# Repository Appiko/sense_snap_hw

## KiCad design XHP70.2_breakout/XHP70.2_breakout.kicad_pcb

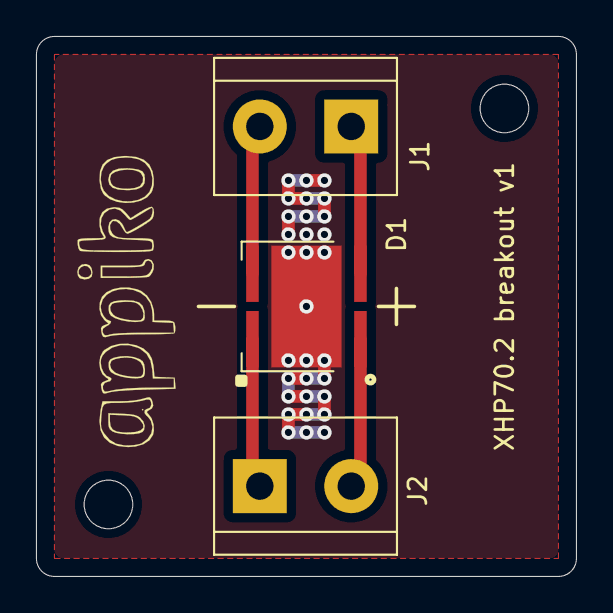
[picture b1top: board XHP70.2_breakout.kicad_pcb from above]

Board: 2 copper layers, 30.0 x 30.0 mm, 3 parts (0 on the bottom side), 4 nets.

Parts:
D1: XHP70.2; LED_Cree-XHP70
J1, J2: Screw_Terminal_01x02; TerminalBlock_bornier-2_P5.08mm

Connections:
unnamed: D1.1, J1.2
unnamed: D1.2, J2.1
unnamed: D1.3, J2.2
unnamed: D1.4, J1.1

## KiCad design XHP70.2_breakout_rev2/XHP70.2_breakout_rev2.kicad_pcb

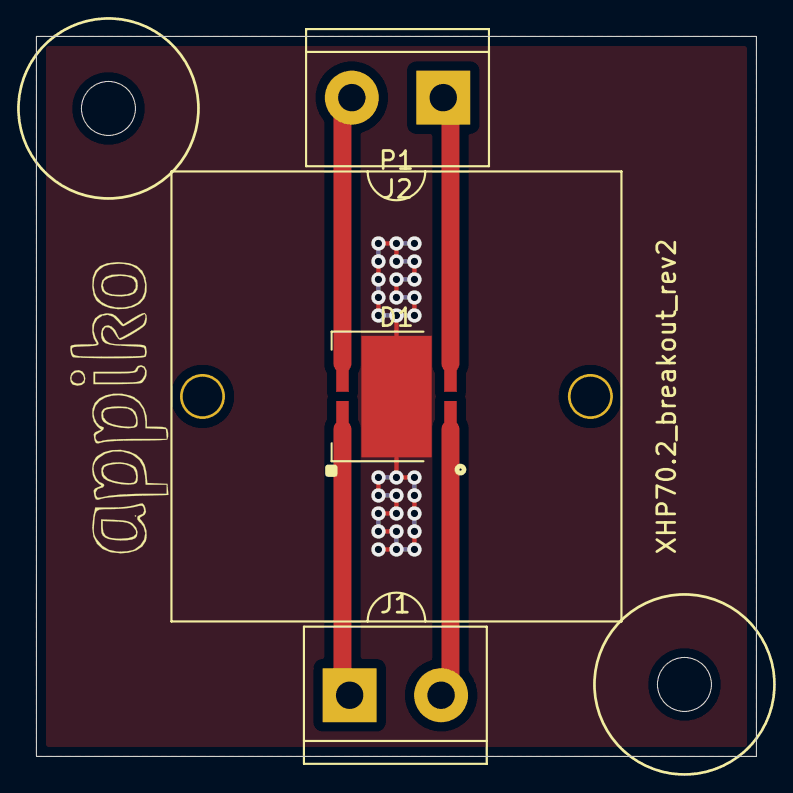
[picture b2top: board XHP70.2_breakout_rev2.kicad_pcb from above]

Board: 2 copper layers, 40.0 x 40.0 mm, 6 parts (0 on the bottom side), 4 nets.

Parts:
D1: XHP70.2; LED_Cree-XHP70
J1, J2: Screw_Terminal_01x02; TerminalBlock_bornier-2_P5.08mm
MK1, MK2: Mounting_Hole_3mm; MountingHole_3mm
P1: CA16372_HB-SQ-WWW

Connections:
unnamed: D1.1, J2.2
unnamed: D1.2, J1.1
unnamed: D1.3, J1.2
unnamed: D1.4, J2.1

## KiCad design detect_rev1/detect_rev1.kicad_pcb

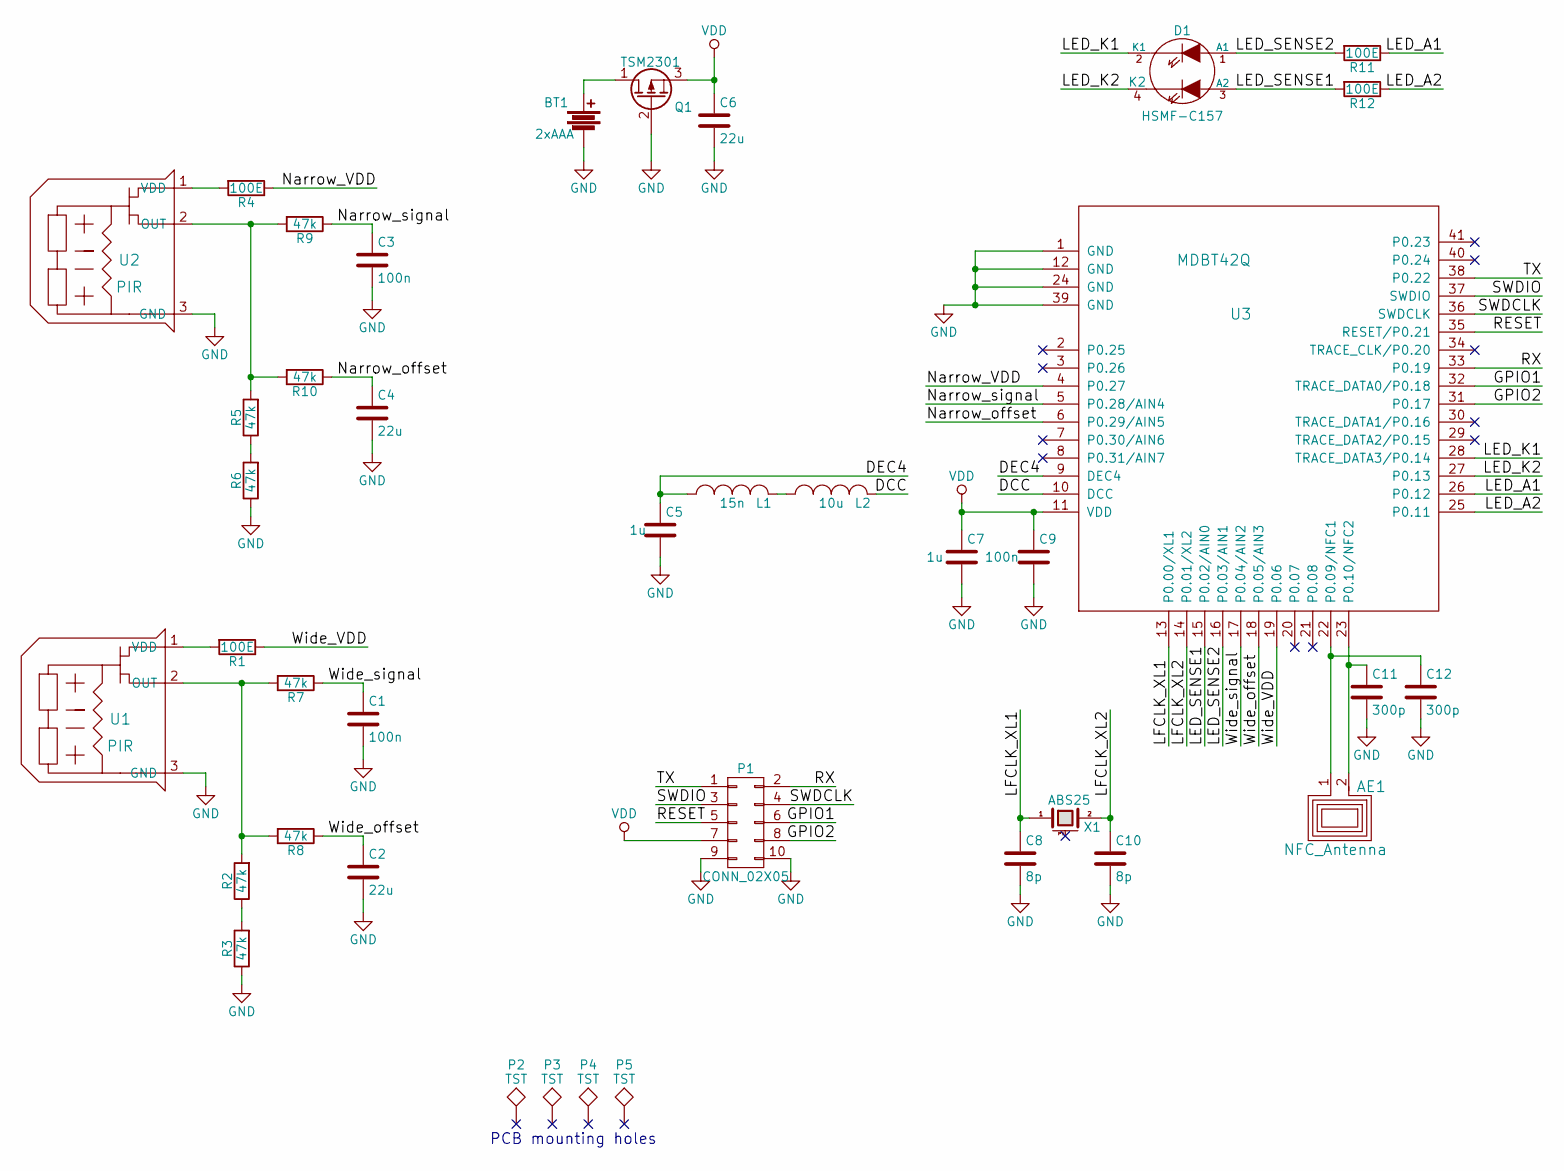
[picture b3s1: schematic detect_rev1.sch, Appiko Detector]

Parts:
AE1: NFC_Antenna; GS2
BT1: 2xAAA; AAA_holder_2468; Part Number 2468
C1, C3, C9: 100n; C_0805
C2, C4, C6: 22u; C_1206; Rating >10V
C5, C7: 1u; C_0805
C8, C10: 8p; C_0805
C11, C12: 300p; C_0805
D1: HSMF-C157; HSMF-C15x; Part Number HSMF-C157
L1: 15n; C_0603
L2: 10u; C_0805
P1: CONN_02X05; Berg_5x2Conn
P2, P3, P4, P5: TST; MountingHole_4.3mm_M4
Q1: TSM2301; Part Number TSM2301CX
R1, R4, R11, R12: 100E; R_0805
R2, R3, R5, R6, R7, R8, R9, R10: 47k; R_0805
U1: PIR; PIR_TO5
U2: PIR; PIR_TO5; Part Number D203B LHi968
U3: MDBT42Q; mdbt42Q
X1: ABS25; ABS25-32.768; Part Number ABS25-32.768KHZ-6-T

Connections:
/DCC: L2.2, U3.10 (DCC)
/DEC4: C5.1, L1.1, U3.9 (DEC4)
/GPIO1: P1.6, U3.32 (TRACE_DATA0/P0.18)
/GPIO2: P1.8, U3.31 (P0.17)
/LED_A1: R11.1, U3.26 (P0.12)
/LED_A2: R12.1, U3.25 (P0.11)
/LED_K1: D1.2 (K1), U3.28 (TRACE_DATA3/P0.14)
/LED_K2: D1.4 (K2), U3.27 (P0.13)
/LED_SENSE1: D1.3 (A2), R12.2, U3.15 (P0.02/AIN0)
/LED_SENSE2: D1.1 (A1), R11.2, U3.16 (P0.03/AIN1)
/LFCLK_XL1: C8.1, U3.13 (P0.00/XL1), X1.1
/LFCLK_XL2: C10.1, U3.14 (P0.01/XL2), X1.2
/Narrow_VDD: R4.1, U3.4 (P0.27)
/Narrow_offset: C4.1, R10.1, U3.6 (P0.29/AIN5)
/Narrow_signal: C3.1, R9.1, U3.5 (P0.28/AIN4)
/RESET: P1.5, U3.35 (RESET/P0.21)
/RX: P1.2, U3.33 (P0.19)
/SWDCLK: P1.4, U3.36 (SWDCLK)
/SWDIO: P1.3, U3.37 (SWDIO)
/TX: P1.1, U3.38 (P0.22)
/Wide_VDD: R1.1, U3.19 (P0.06)
/Wide_offset: C2.1, R8.1, U3.18 (P0.05/AIN3)
/Wide_signal: C1.1, R7.1, U3.17 (P0.04/AIN2)
GND: BT1.2, C1.2, C2.2, C3.2, C4.2, C5.2, C6.2, C7.2, C8.2, C9.2, C10.2, C11.2, C12.2, P1.9, P1.10, Q1.2 (G), R3.1, R6.1, U1.3 (GND), U2.3 (GND), U3.1 (GND), U3.12 (GND), U3.24 (GND), U3.39 (GND)
unnamed: AE1.1, C12.1, U3.22 (P0.09/NFC1)
unnamed: AE1.2, C11.1, U3.23 (P0.10/NFC2)
unnamed: BT1.1, Q1.1 (D)
unnamed: L1.2, L2.1
unnamed: R1.2, U1.1 (VDD)
unnamed: R2.1, R3.2
unnamed: R2.2, R7.2, R8.2, U1.2 (OUT)
unnamed: R4.2, U2.1 (VDD)
unnamed: R5.1, R6.2
unnamed: R5.2, R9.2, R10.2, U2.2 (OUT)
VDD: C6.1, C7.1, C9.1, P1.7, Q1.3 (S), U3.11 (VDD)

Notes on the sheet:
PCB mounting holes

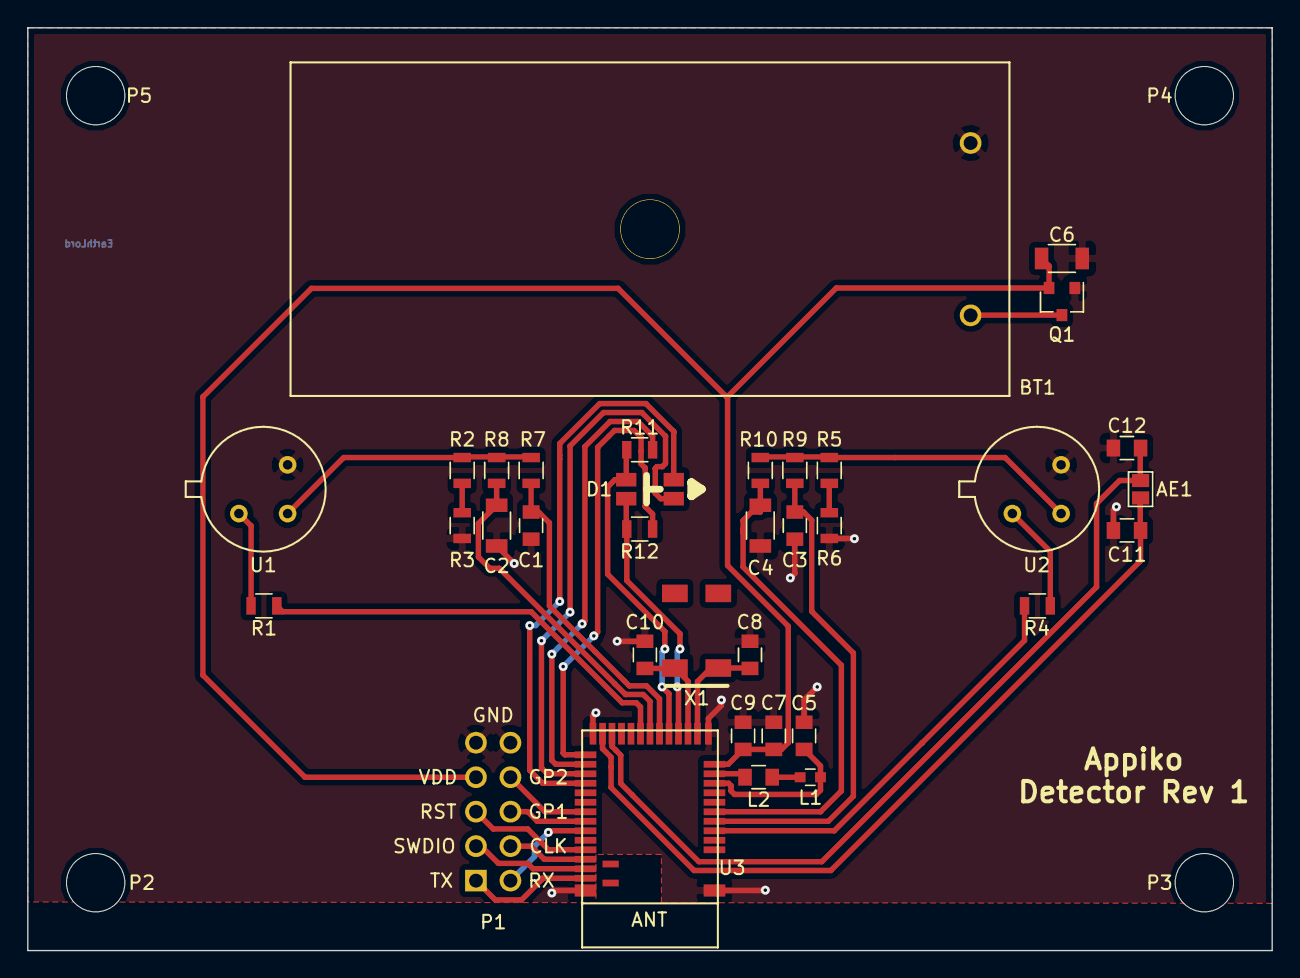
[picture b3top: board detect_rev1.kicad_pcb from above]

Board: 2 copper layers, 91.7 x 68.0 mm, 39 parts (0 on the bottom side), 35 nets.

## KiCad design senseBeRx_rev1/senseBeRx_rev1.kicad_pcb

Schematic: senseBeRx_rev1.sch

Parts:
BT1: Battery; BT_Symbol
C1, C3: 1uF; C_0603_1608Metric_Pad1.05x0.95mm_HandSolder
C2: 10uF; C_0805_2012Metric_Pad1.15x1.40mm_HandSolder
C4, C6: 8pF; C_0603_1608Metric_Pad1.05x0.95mm_HandSolder
C5, C7, C8: 100nF; C_0603_1608Metric_Pad1.05x0.95mm_HandSolder
D1: APBD3224SURKCGKC-F01; LED_APBD3224SURKCGKC-F01
D2: D_Photo; LED_D5.0mm
J1, J2: SJ2-35863B1-SMT
L1: 15nH; L_0603_1608Metric_Pad1.05x0.95mm_HandSolder
L2: 10nH; L_0603_1608Metric_Pad1.05x0.95mm_HandSolder
MK1, MK2: Mounting_Hole; MountingHole_3.2mm_M3
P1: CONN_02X05; prog_connect
Q1: TSM2301; SOT-23_Handsoldering
Q2, Q3, Q4: SI2302; SOT-23_Handsoldering
R1, R4, R5, R7, R8, R9: 100k; R_0603_1608Metric_Pad1.05x0.95mm_HandSolder
R2: 33; R_0603_1608Metric_Pad1.05x0.95mm_HandSolder
R3: 24; R_0603_1608Metric_Pad1.05x0.95mm_HandSolder
R6: 3M; R_0603_1608Metric_Pad1.05x0.95mm_HandSolder
SW1: SW_DPST; SW_TH_Tactile_Omron_B3F-10xx
U1: MDBT42Q; mdbt42Q
U2: TSSP4056; Vishay_MINIMOLD-3Pin
Y1: T38 Mercury; Crystal_C38-LF_D3.0mm_L8.0mm_Horizontal

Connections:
/BUTTON: C8.2, SW1.4, U1.21
/CAM_JACK: J1.4, R8.2, U1.25
/DCC: L2.2, U1.10
/DEC4: C1.2, L1.1, U1.9
/FOCUS: J1.3, U1.26
/GPIO1: P1.6, U1.33
/GPIO2: P1.7, U1.32
/LED_GREEN: Q2.1 (G), R1.1, U1.2
/LED_RED: Q3.1 (G), R4.1, U1.3
/LFCLK_XL1: C4.2, U1.13, Y1.1
/LFCLK_XL2: C6.2, U1.14, Y1.2
/LIGHT_SENSE: D2.1, R5.2, U1.18
/RESET: P1.5, U1.35
/RX: P1.8, U1.31
/RX_EN: Q4.1 (G), R7.1, U1.20
/RX_OUT: U1.19, U2.1
/RX_UARTRX: J2.3, U1.29
/RX_UARTTX: J2.2, U1.30
/SWDCLK: P1.3, U1.36
/SWDIO: P1.1, U1.37
/TRIGGER: J1.2, U1.27
/TX: P1.2, U1.34
/UART_JACK: J2.4, R9.2, U1.28
GND: BT1.2, C1.1, C2.2, C3.1, C4.1, C5.1, C6.1, C7.2, C8.1, D2.2, J1.1, J2.1, P1.9, P1.10, Q1.1 (G), Q2.2 (S), Q3.2 (S), Q4.2 (S), R1.2, R4.2, R6.2, R7.2, SW1.3, U1.1, U1.12, U1.24, U1.39
unnamed: BT1.1, Q1.3 (D)
unnamed: D1.2, R2.2
unnamed: D1.4, R3.2
unnamed: L1.2, L2.1
unnamed: Q2.3 (D), R3.1
unnamed: Q3.3 (D), R2.1
unnamed: Q4.3 (D), R6.1, U2.2
VDD: C2.1, C3.2, C5.2, C7.1, D1.1, D1.3, P1.4, Q1.2 (S), R5.1, R8.1, R9.1, U1.8, U1.11, U2.3

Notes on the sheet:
Two 1.2V AA Batteries
Reverse polarity protection
Two Color (Green/Red) LED
A momentary push button with debouncing cap to switch to config. mode
To use the Internal DC/DC Converter we need an LC Filter
For programming and debugging the nRF controller
Low freq. Crystal 32.768 kHz
IR pattern receiver with an enable switch
Ambient light sensing
Port to trigger the camera
Port for the UART communication between the SenseBe Rx and Tx units

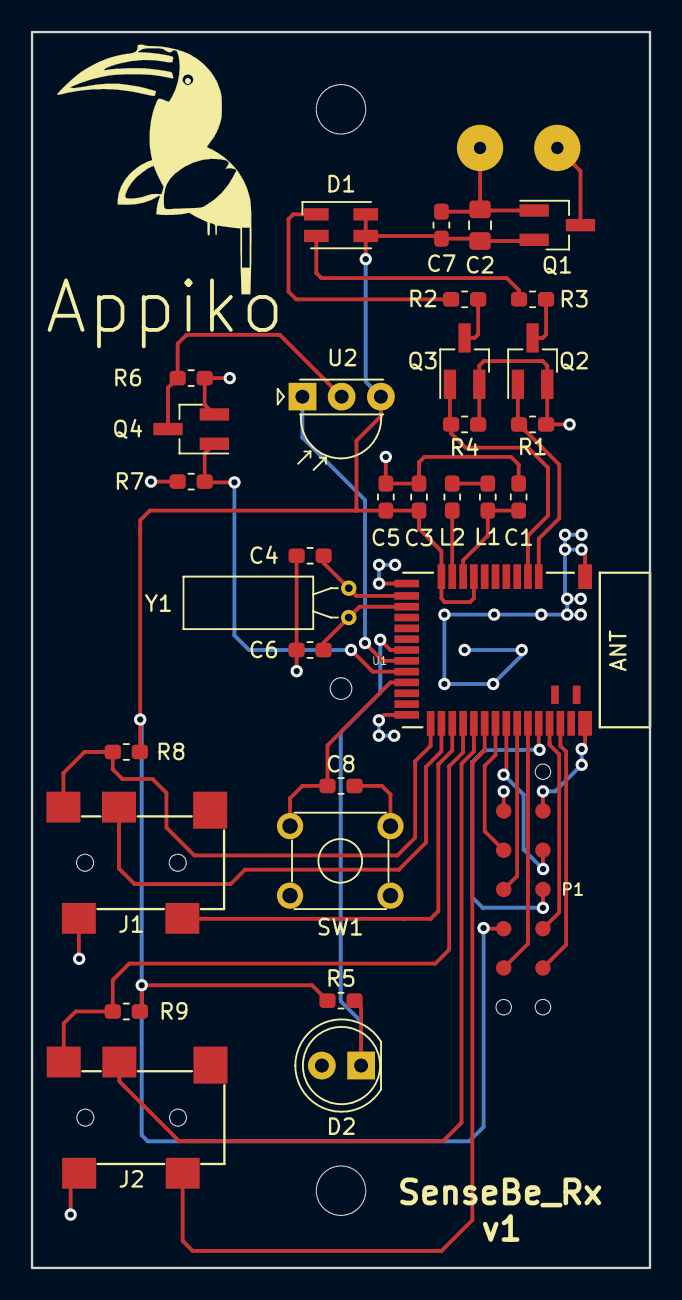
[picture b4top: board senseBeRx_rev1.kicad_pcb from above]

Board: 2 copper layers, 40.0 x 80.0 mm, 33 parts (1 on the bottom side), 32 nets.

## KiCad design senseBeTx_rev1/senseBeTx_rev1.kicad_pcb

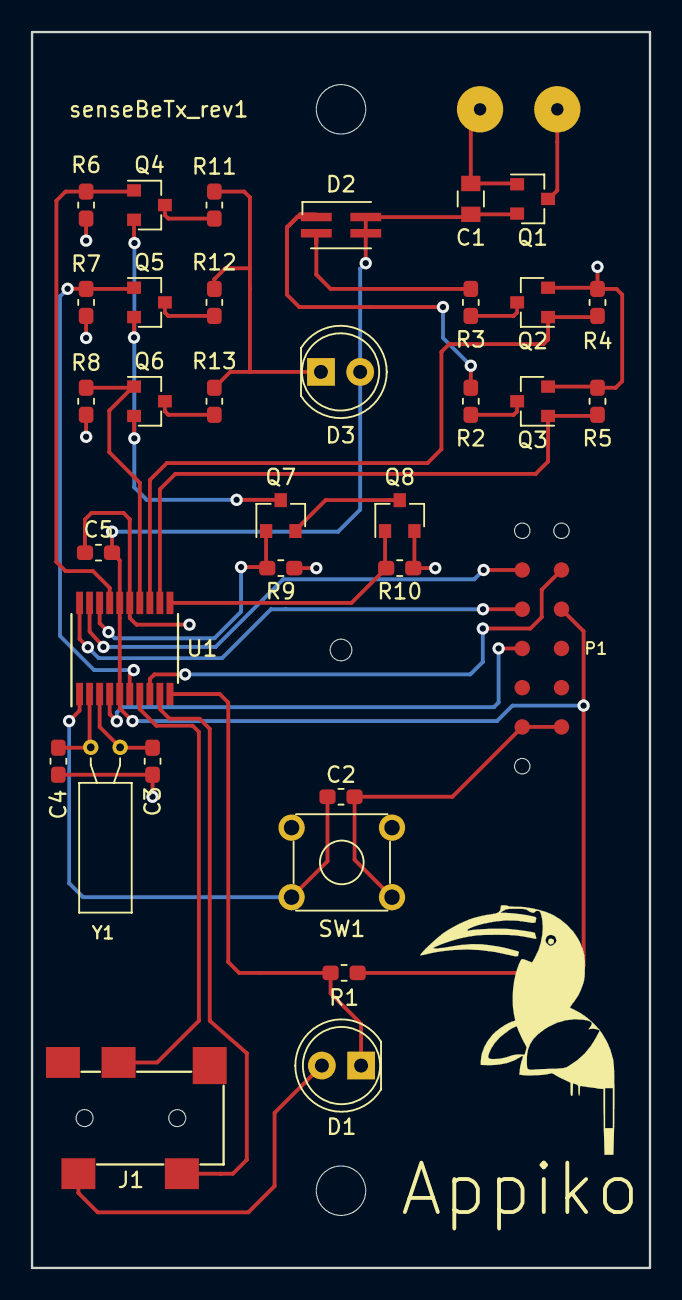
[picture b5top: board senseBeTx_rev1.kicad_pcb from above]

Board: 2 copper layers, 40.0 x 80.0 mm, 35 parts (1 on the bottom side), 30 nets.

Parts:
BT1: Battery; BT_Symbol
C1: 10uF; C_0805
C2, C5: 100nF; C_0603_1608Metric_Pad1.05x0.95mm_HandSolder
C3, C4: 8pF; C_0603_1608Metric_Pad1.05x0.95mm_HandSolder
D1: D_Photo; LED_D5.0mm
D2: KPTBD-3216SURKCGKC; LED_KPTBD-3216SURKCGKC
D3: SFH4546; LED_D5.0mm_IRGrey
J1: Audio-Jack-4_1Switches; SJ2-35863B1-SMT
P1: CONN_02X05; prog_connect
Q1: SI2301; SOT-23
Q2, Q3, Q4, Q5, Q6, Q7, Q8: SI2302; SOT-23
R1, R4, R5, R6, R7, R8, R9, R10: 100k; R_0603_1608Metric_Pad1.05x0.95mm_HandSolder
R2: 33E; R_0603_1608Metric_Pad1.05x0.95mm_HandSolder
R3: 24E; R_0603_1608Metric_Pad1.05x0.95mm_HandSolder
R11: 20E; R_0603_1608Metric_Pad1.05x0.95mm_HandSolder
R12: 12E; R_0603_1608Metric_Pad1.05x0.95mm_HandSolder
R13: 4.7E; R_0603_1608Metric_Pad1.05x0.95mm_HandSolder
SW1: SW_Push_Dual; SW_TH_Tactile_Omron_B3F-10xx
U1: STM32L011F3Px; TSSOP-20_4.4x6.5mm_P0.65mm
Y1: Crystal; Crystal_C38-LF_d3.0mm_l8.0mm_Horizontal

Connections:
/4R7: Q6.3, R13.1
/BUTTON: C2.1, SW1.2, U1.1
/LEDIR_CNTRL1: Q7.1, R9.2, U1.18
/LEDIR_CNTRL2: Q8.1, R10.2, U1.11
/LEDIR_PWR1: Q4.1, R6.2, U1.17
/LEDIR_PWR2: Q5.1, R7.2, U1.6
/LEDIR_PWR3: Q6.1, R8.2, U1.14
/LED_GREEN: Q2.1, R4.2, U1.13
/LED_RED: Q3.1, R5.2, U1.12
/LIGHT_SENSE: D1.1, R1.2, U1.10
/LPUART1_RX: J1.2, U1.9
/LPUART1_TX: J1.3, U1.7
/R12: Q5.3, R12.1
/R20: Q4.3, R11.1
/RCC_OSC32_IN: C4.1, U1.2, Y1.1
/RCC_OSC32_OUT: C3.1, U1.3, Y1.2
/RESET: P1.5, U1.4
/R_CNTRL: Q4.2, Q5.2, Q6.2, Q7.3
/SYS_SWDCLK: P1.3, U1.20
/SYS_SWDIO: P1.1, U1.19
/USART2_TX: P1.2, U1.8
GND: BT1.2, C1.2, C2.2, C3.2, C4.2, C5.1, D1.2, J1.1, P1.9, P1.10, Q1.1, Q2.2, Q3.2, Q8.2, R4.1, R5.1, R6.1, R7.1, R8.1, R9.1, R10.1, SW1.1, U1.15
unnamed: BT1.1, Q1.3
unnamed: D2.2, R2.2
unnamed: D2.4, R3.2
unnamed: D3.1, R11.2, R12.2, R13.2
unnamed: Q2.3, R3.1
unnamed: Q3.3, R2.1
unnamed: Q7.2, Q8.3
VDD: C1.1, C5.2, D2.1, D2.3, D3.2, P1.4, Q1.2, R1.1, U1.5, U1.16

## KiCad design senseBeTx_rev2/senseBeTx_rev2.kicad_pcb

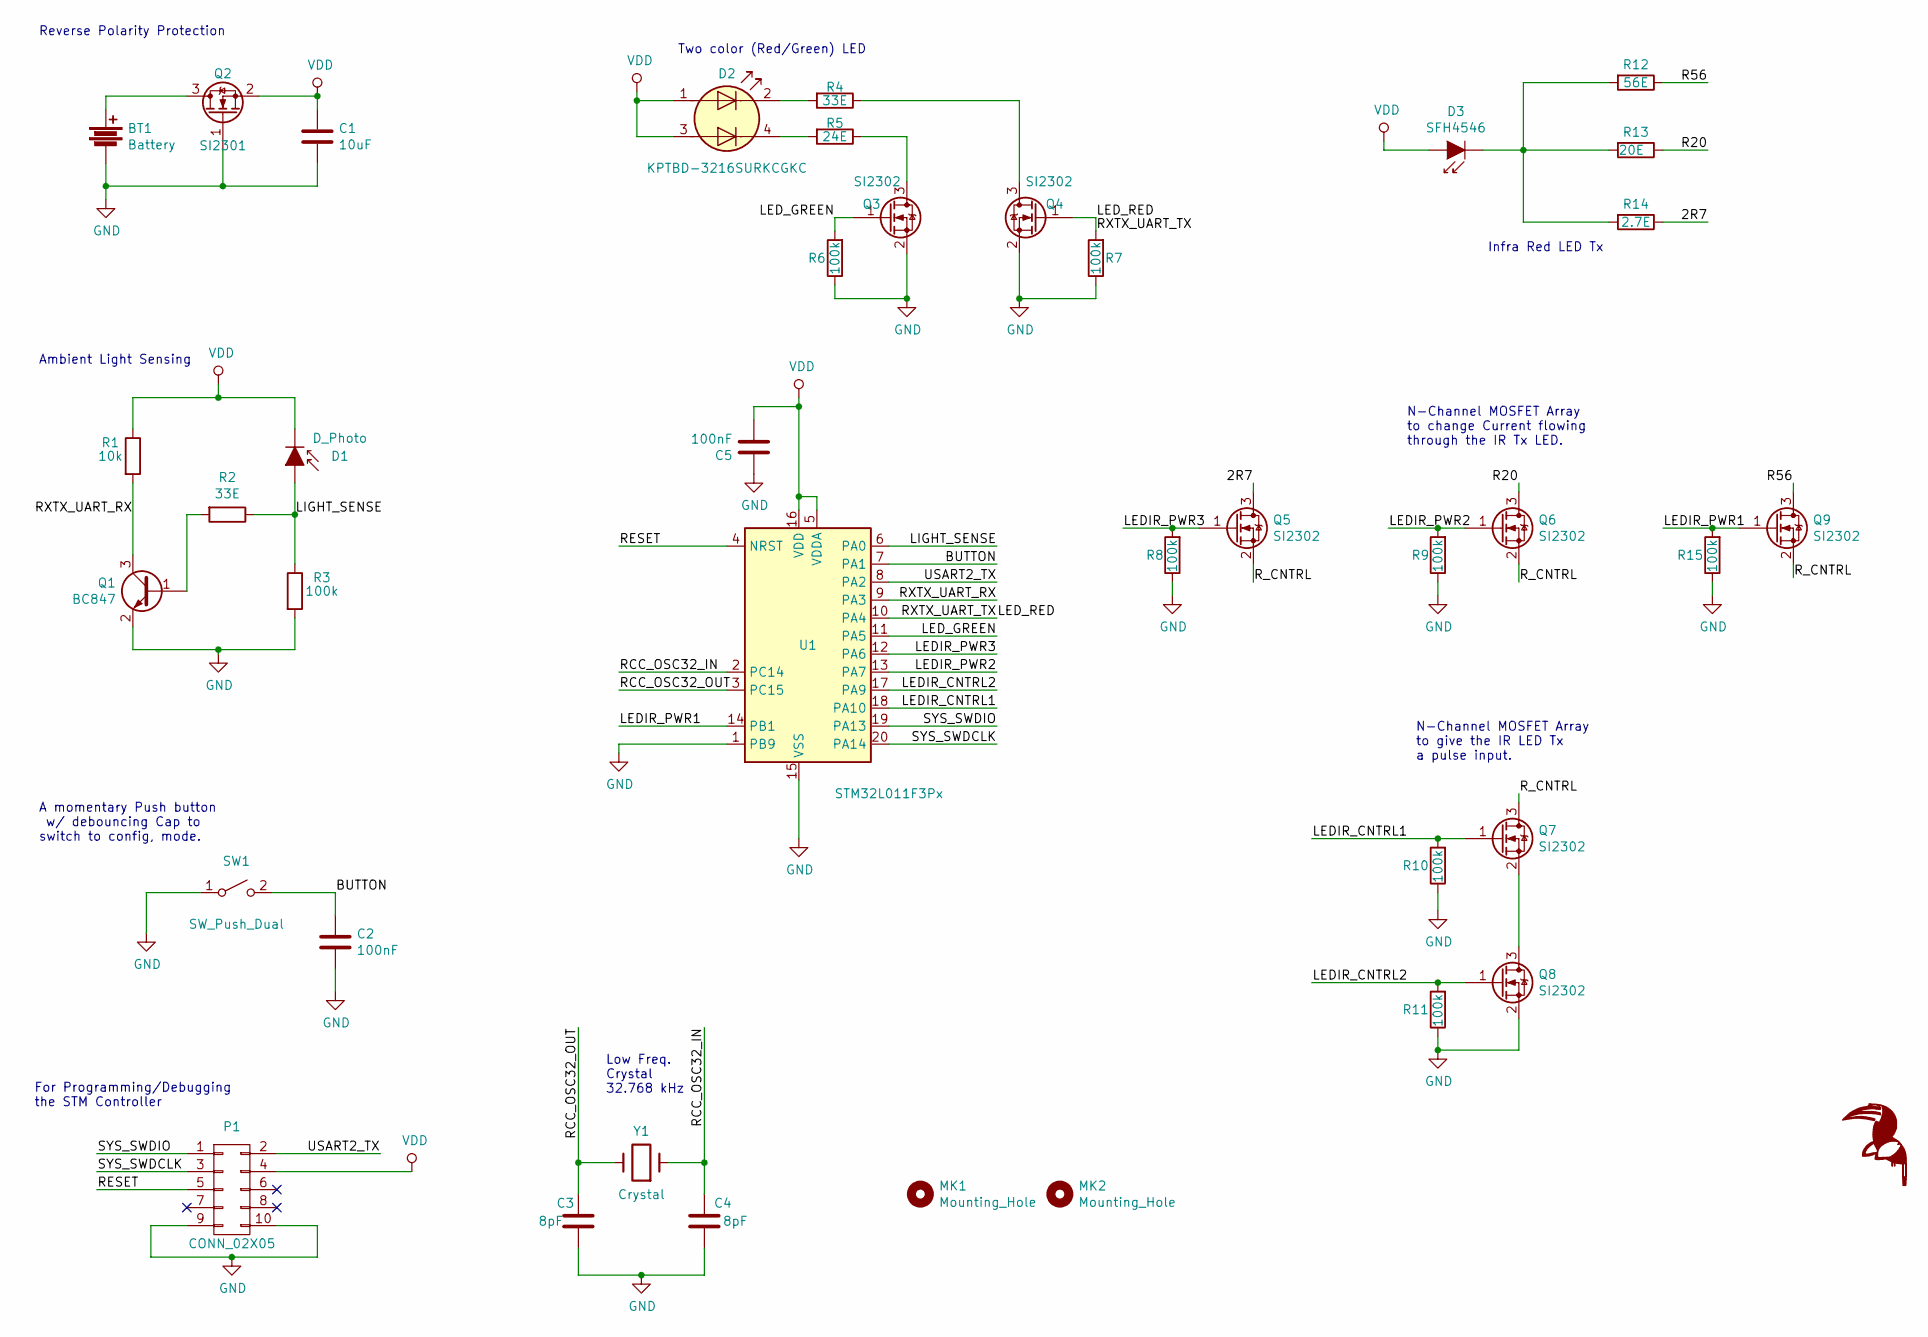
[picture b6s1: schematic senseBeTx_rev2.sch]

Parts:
BT1: Battery; BT_Symbol
C1: 10uF; C_0805
C2, C5: 100nF; C_0603_1608Metric_Pad1.05x0.95mm_HandSolder
C3, C4: 8pF; C_0603_1608Metric_Pad1.05x0.95mm_HandSolder
D1: D_Photo; LED_D5.0mm
D2: KPTBD-3216SURKCGKC; LED_KPTBD-3216SURKCGKC
D3: SFH4546; LED_D5.0mm_IRGrey
MK1, MK2: Mounting_Hole; MountingHole_3.2mm_M3
P1: CONN_02X05; prog_connect
Q1: BC847; SOT-23
Q2: SI2301; SOT-23
Q3, Q4, Q5, Q6, Q7, Q8, Q9: SI2302; SOT-23
R1: 10k; R_0603_1608Metric_Pad1.05x0.95mm_HandSolder
R2, R4: 33E; R_0603_1608Metric_Pad1.05x0.95mm_HandSolder
R3, R6, R7, R8, R9, R10, R11, R15: 100k; R_0603_1608Metric_Pad1.05x0.95mm_HandSolder
R5: 24E; R_0603_1608Metric_Pad1.05x0.95mm_HandSolder
R12: 56E; R_0603_1608Metric_Pad1.05x0.95mm_HandSolder
R13: 20E; R_0603_1608Metric_Pad1.05x0.95mm_HandSolder
R14: 2.7E; R_0603_1608Metric_Pad1.05x0.95mm_HandSolder
SW1: SW_Push_Dual; SW_PUSH_6mm
U1: STM32L011F3Px; TSSOP-20_4.4x6.5mm_P0.65mm
Y1: Crystal; Crystal_C38-LF_d3.0mm_l8.0mm_Horizontal

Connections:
/2R7: Q5.3 (D), R14.1
/BUTTON: C2.1, SW1.2 (B), U1.7 (PA1)
/LEDIR_CNTRL1: Q7.1 (G), R10.2, U1.18 (PA10)
/LEDIR_CNTRL2: Q8.1 (G), R11.2, U1.17 (PA9)
/LEDIR_PWR1: Q9.1 (G), R15.2, U1.14 (PB1)
/LEDIR_PWR2: Q6.1 (G), R9.2, U1.13 (PA7)
/LEDIR_PWR3: Q5.1 (G), R8.2, U1.12 (PA6)
/LED_GREEN: Q3.1 (G), R6.2, U1.11 (PA5)
/LED_RED: Q4.1 (G), R7.2, U1.10 (PA4)
/LIGHT_SENSE: D1.2 (A), R2.1, R3.1, U1.6 (PA0)
/R20: Q6.3 (D), R13.1
/R56: Q9.3 (D), R12.1
/RCC_OSC32_IN: C4.1, U1.2 (PC14), Y1.1
/RCC_OSC32_OUT: C3.1, U1.3 (PC15), Y1.2
/RESET: P1.5, U1.4 (NRST)
/RXTX_UART_RX: Q1.3 (C), R1.2, U1.9 (PA3)
/R_CNTRL: Q5.2 (S), Q6.2 (S), Q7.3 (D), Q9.2 (S)
/SYS_SWDCLK: P1.3, U1.20 (PA14)
/SYS_SWDIO: P1.1, U1.19 (PA13)
/USART2_TX: P1.2, U1.8 (PA2)
unnamed: BT1.1, Q2.3 (D)
unnamed: D2.2 (K1), R4.2
unnamed: D2.4 (K2), R5.2
unnamed: D3.1 (K), R12.2, R13.2, R14.2
unnamed: Q1.1 (B), R2.2
unnamed: Q3.3 (D), R5.1
unnamed: Q4.3 (D), R4.1
unnamed: Q7.2 (S), Q8.3 (D)
VDD: C1.1, C5.2, D1.1 (K), D2.1 (A1), D2.3 (A2), D3.2 (A), P1.4, Q2.2 (S), R1.1, U1.5 (VDDA), U1.16 (VDD)

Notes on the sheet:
Reverse Polarity Protection
A momentary Push button w/ debouncing Cap to switch to config, mode.
Ambient Light Sensing
For Programming/Debugging the STM Controller
Low Freq. Crystal 32.768 kHz
Two color (Red/Green) LED
N-Channel MOSFET Array to change Current flowing through the IR Tx LED.
N-Channel MOSFET Array to give the IR LED Tx a pulse input.
Infra Red LED Tx

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
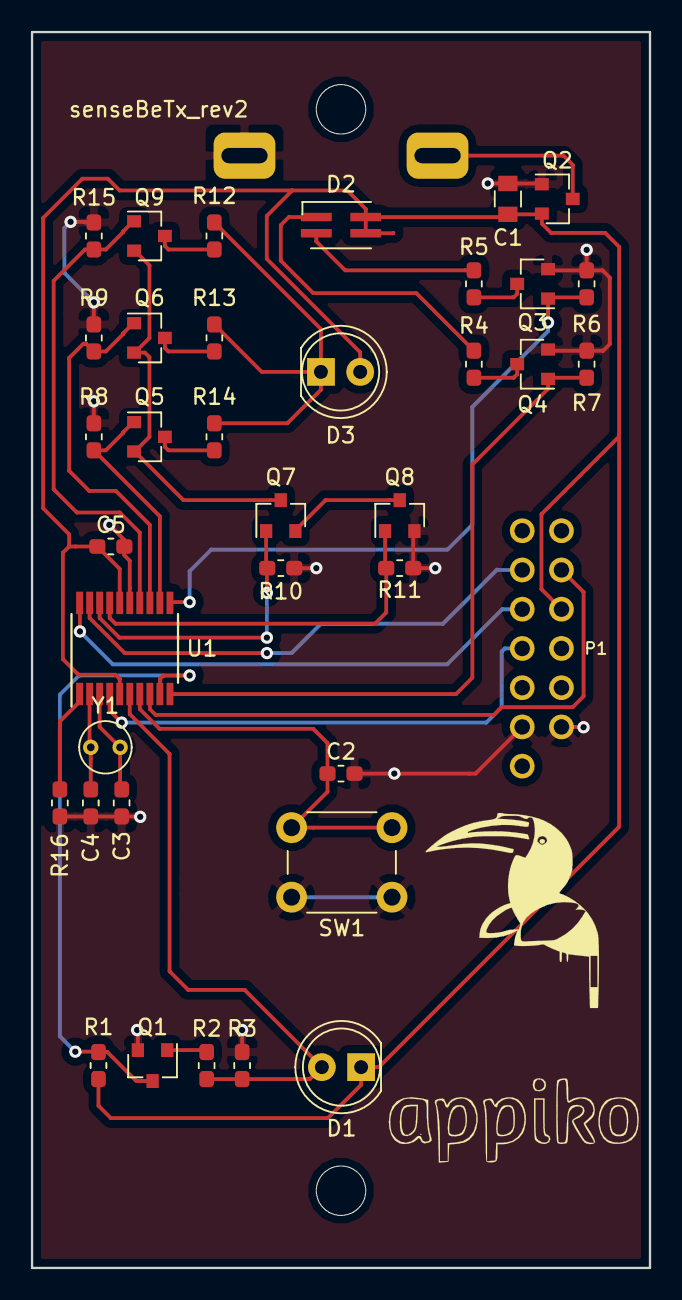
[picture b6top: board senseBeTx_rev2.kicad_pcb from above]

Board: 2 copper layers, 40.0 x 80.0 mm, 38 parts (1 on the bottom side), 31 nets.

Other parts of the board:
R16: 100k; R_0603_1608Metric_Pad1.05x0.95mm_HandSolder
